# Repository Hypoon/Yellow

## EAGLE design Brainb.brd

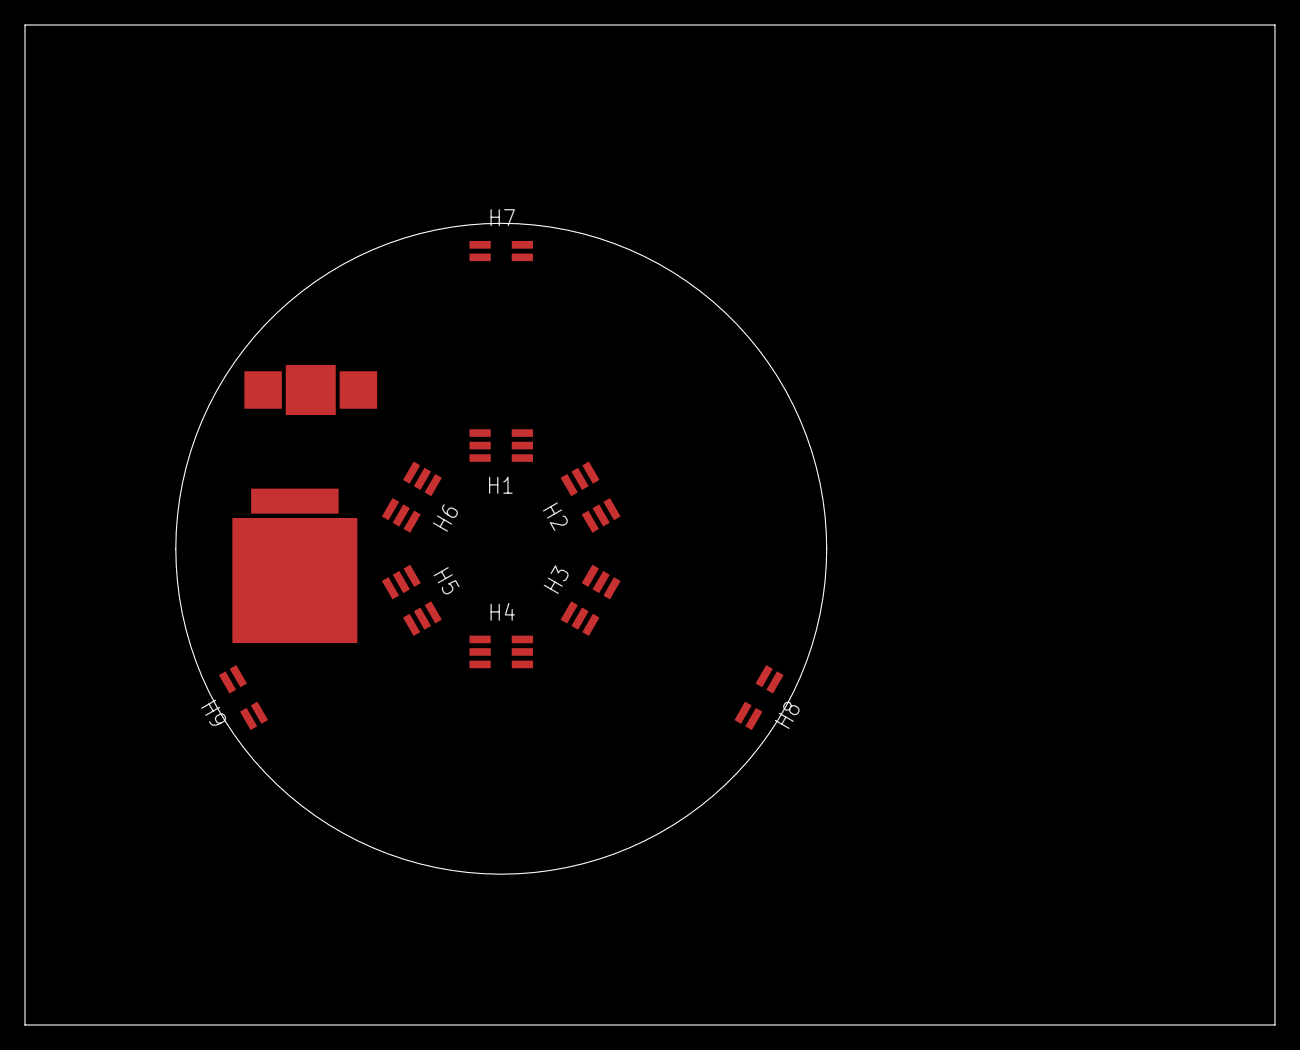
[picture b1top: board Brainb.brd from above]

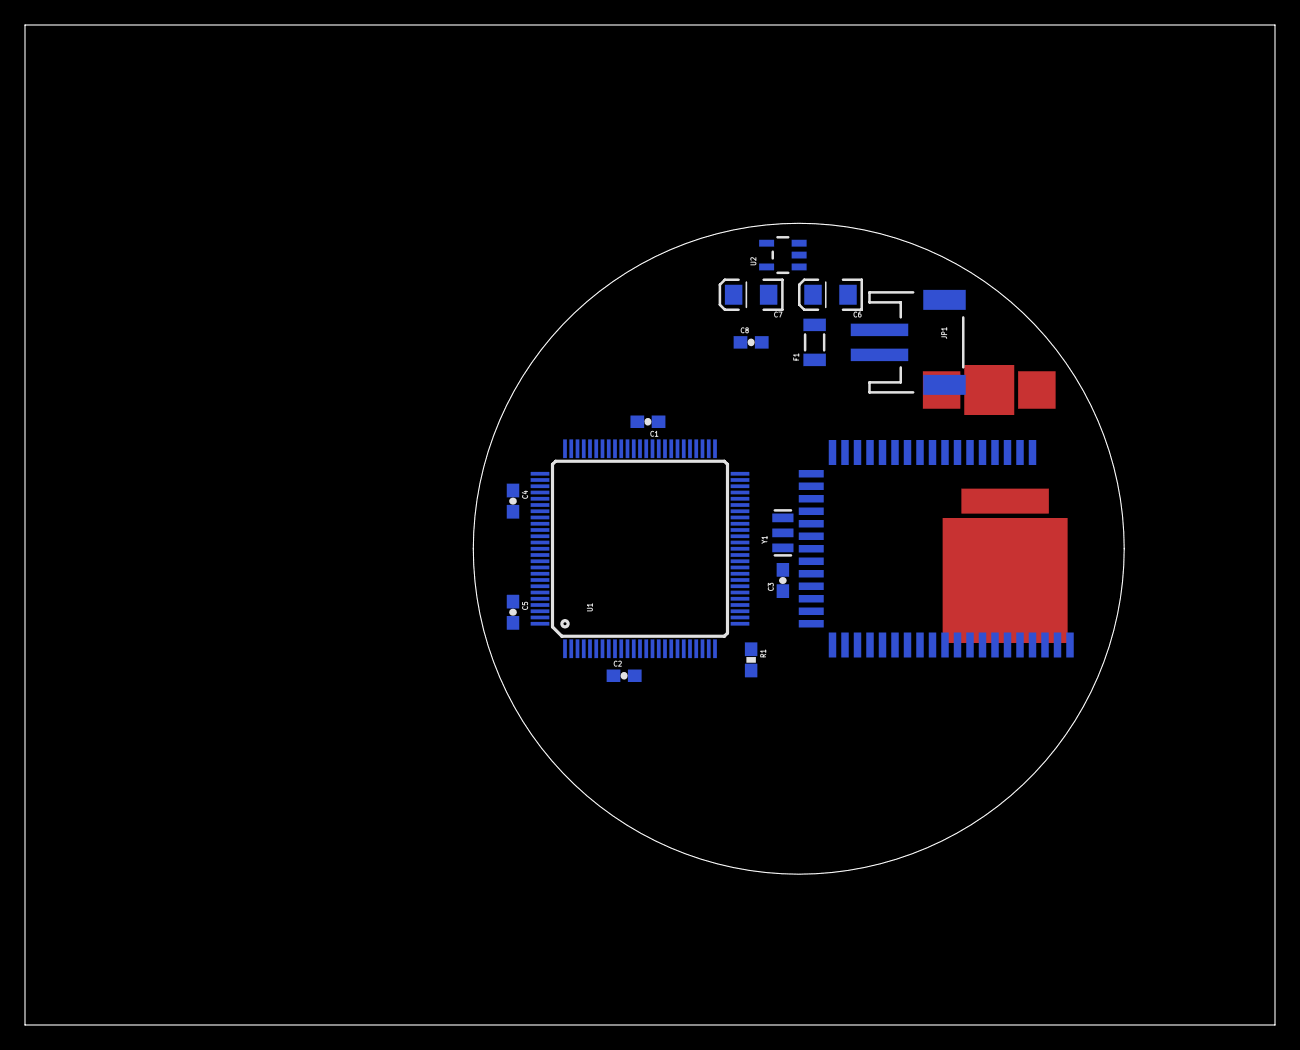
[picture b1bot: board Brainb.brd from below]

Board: 2 copper layers, 100.0 x 80.0 mm, 24 parts (15 on the bottom side), 8 nets, no tracks yet.

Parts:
C1, C2, C3, C4, C5, C8: 0.1uF; 0603-CAP
C6, C7: 10uF; EIA3216
F1: PTCSMD; PTC-1206
H1, H2, H3, H4, H5, H6: 3X2F_1MM_SMD
H7, H8, H9: 2X2F_1MM_SMD
IC1: WT32WT32; WT32
JP1: JST-2-SMD
R1: 10k; 0603-RES
U1: ATMEGA2560AU; TQFP100
U2: MIC5219-3.3; SOT23-5
Y1: 8MHz; RESONATOR-SMD

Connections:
+3V3: C1.1, C2.1, C3.1, C4.1, C7.A, C8.1, R1.2, U1.10, U1.31, U1.61, U1.80, U1.100, U2.5
GND: C1.2, C2.2, C3.2, C4.2, C5.2, C6.C, C7.C, C8.2, JP1.1, U1.11, U1.32, U1.62, U1.81, U1.99, U2.2, Y1.2
unnamed: C5.1, U1.98
unnamed: U1.34, Y1.3
unnamed: U1.33, Y1.1
unnamed: F1.1, JP1.2
unnamed: R1.1, U1.30
unnamed: C6.A, F1.2, U2.1, U2.3

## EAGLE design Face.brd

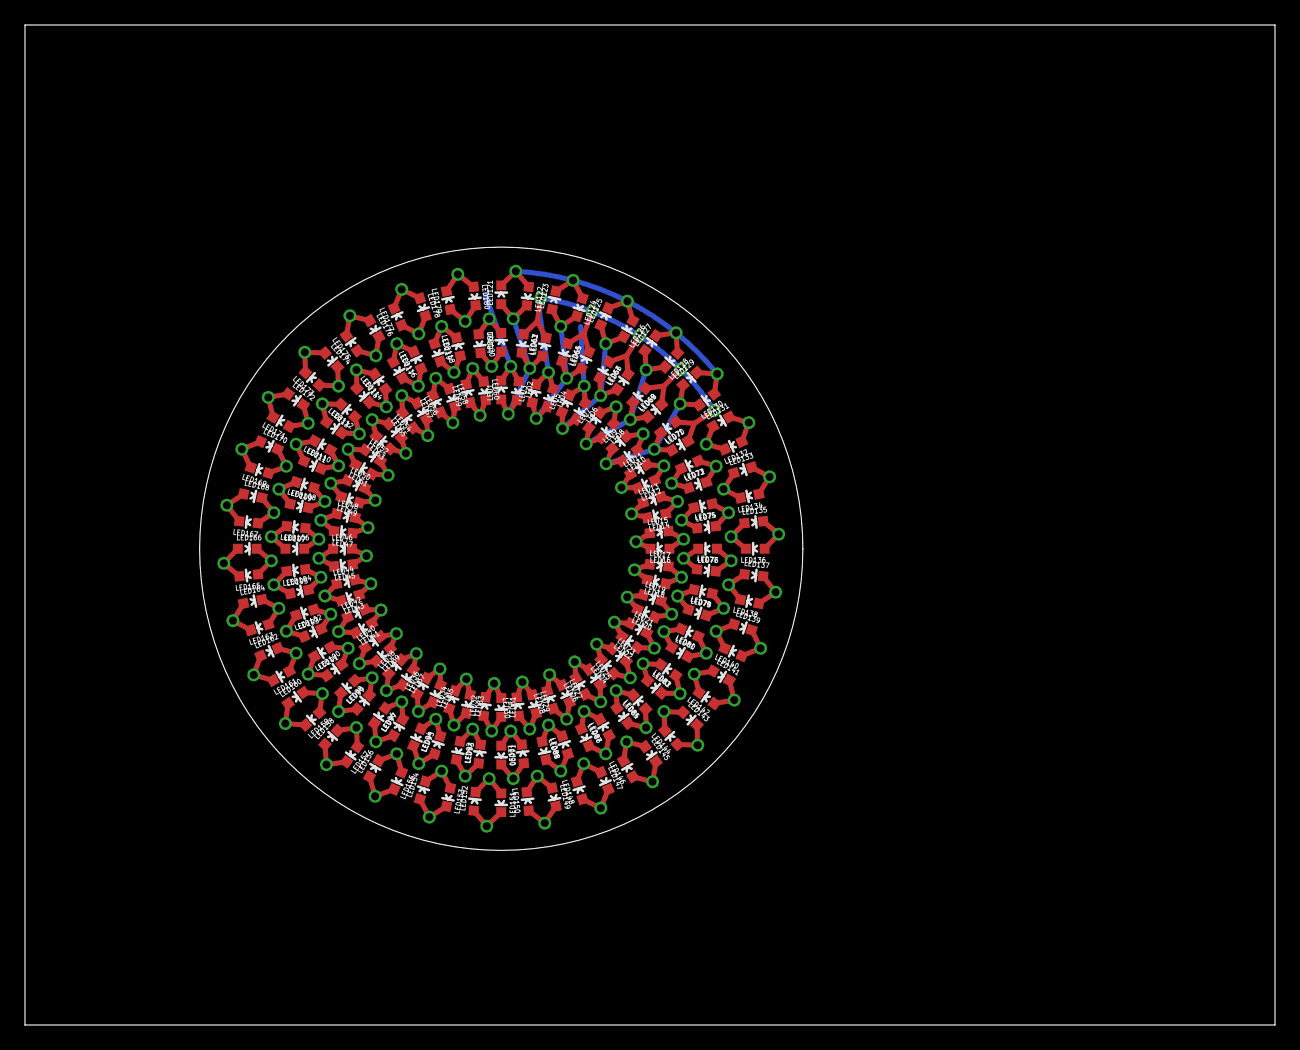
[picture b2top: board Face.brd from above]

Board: 2 copper layers, 100.0 x 80.0 mm, 180 parts (0 on the bottom side), 158 nets.

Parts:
LED1, LED2, LED3, LED4, LED5, LED6, LED7, LED8, LED9, LED10, LED11, LED12, LED13, LED14, LED15, LED16, LED17, LED18, LED19, LED20, LED21, LED22, LED23, LED24, LED25, LED26, LED27, LED28, LED29, LED30, LED31, LED32, LED33, LED34, LED35, LED36, LED37, LED38, LED39, LED40, LED41, LED42, LED43, LED44, LED45, LED46, LED47, LED48, LED49, LED50, LED51, LED52, LED53, LED54, LED55, LED56, LED57, LED58, LED59, LED60, LED61, LED62, LED63, LED64, LED65, LED66, LED67, LED68, LED69, LED70, LED71, LED72, LED73, LED74, LED75, LED76, LED77, LED78, LED79, LED80, LED81, LED82, LED83, LED84, LED85, LED86, LED87, LED88, LED89, LED90, LED91, LED92, LED93, LED94, LED95, LED96, LED97, LED98, LED99, LED100, LED101, LED102, LED103, LED104, LED105, LED106, LED107, LED108, LED109, LED110, LED111, LED112, LED113, LED114, LED115, LED116, LED117, LED118, LED119, LED120, LED121, LED122, LED123, LED124, LED125, LED126, LED127, LED128, LED129, LED130, LED131, LED132, LED133, LED134, LED135, LED136, LED137, LED138, LED139, LED140, LED141, LED142, LED143, LED144, LED145, LED146, LED147, LED148, LED149, LED150, LED151, LED152, LED153, LED154, LED155, LED156, LED157, LED158, LED159, LED160, LED161, LED162, LED163, LED164, LED165, LED166, LED167, LED168, LED169, LED170, LED171, LED172, LED173, LED174, LED175, LED176, LED177, LED178, LED179, LED180: RED; LED-0603

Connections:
unnamed: LED1.A, LED2.C, LED62.C, LED63.A, LED121.A, LED122.C
unnamed: LED3.A, LED4.C, LED64.C, LED65.A, LED123.A, LED124.C
unnamed: LED5.A, LED6.C, LED66.C, LED67.A, LED125.A, LED126.C
unnamed: LED7.A, LED8.C, LED68.C, LED69.A, LED127.A, LED128.C
unnamed: LED9.A, LED10.C, LED70.C, LED71.A, LED129.A, LED130.C
unnamed: LED11.A, LED12.C
unnamed: LED13.A, LED14.C
unnamed: LED15.A, LED16.C
unnamed: LED17.A, LED18.C
unnamed: LED19.A, LED20.C
unnamed: LED21.A, LED22.C
unnamed: LED23.A, LED24.C
unnamed: LED25.A, LED26.C
unnamed: LED27.A, LED28.C
unnamed: LED29.A, LED30.C
unnamed: LED31.A, LED32.C
unnamed: LED33.A, LED34.C
unnamed: LED35.A, LED36.C
unnamed: LED37.A, LED38.C
unnamed: LED39.A, LED40.C
unnamed: LED41.A, LED42.C
unnamed: LED43.A, LED44.C
unnamed: LED45.A, LED46.C
unnamed: LED47.A, LED48.C
unnamed: LED49.A, LED50.C
unnamed: LED51.A, LED52.C
unnamed: LED53.A, LED54.C
unnamed: LED55.A, LED56.C
unnamed: LED57.A, LED58.C
unnamed: LED59.A, LED60.C
unnamed: LED72.C, LED73.A
unnamed: LED74.C, LED75.A
unnamed: LED76.C, LED77.A
unnamed: LED78.C, LED79.A
unnamed: LED80.C, LED81.A
unnamed: LED82.C, LED83.A
unnamed: LED84.C, LED85.A
unnamed: LED86.C, LED87.A
unnamed: LED88.C, LED89.A
unnamed: LED90.C, LED91.A
unnamed: LED92.C, LED93.A
unnamed: LED94.C, LED95.A
unnamed: LED96.C, LED97.A
unnamed: LED98.C, LED99.A
unnamed: LED100.C, LED101.A
unnamed: LED102.C, LED103.A
unnamed: LED104.C, LED105.A
unnamed: LED106.C, LED107.A
unnamed: LED108.C, LED109.A
unnamed: LED110.C, LED111.A
unnamed: LED112.C, LED113.A
unnamed: LED114.C, LED115.A
unnamed: LED116.C, LED117.A
unnamed: LED118.C, LED119.A
unnamed: LED61.A, LED120.C
unnamed: LED131.A, LED132.C
unnamed: LED133.A, LED134.C
unnamed: LED135.A, LED136.C
unnamed: LED137.A, LED138.C
unnamed: LED139.A, LED140.C
unnamed: LED141.A, LED142.C
unnamed: LED143.A, LED144.C
unnamed: LED145.A, LED146.C
unnamed: LED147.A, LED148.C
unnamed: LED149.A, LED150.C
unnamed: LED151.A, LED152.C
unnamed: LED153.A, LED154.C
unnamed: LED155.A, LED156.C
unnamed: LED157.A, LED158.C
unnamed: LED159.A, LED160.C
unnamed: LED161.A, LED162.C
unnamed: LED163.A, LED164.C
unnamed: LED165.A, LED166.C
unnamed: LED167.A, LED168.C
unnamed: LED169.A, LED170.C
unnamed: LED171.A, LED172.C
unnamed: LED173.A, LED174.C
unnamed: LED175.A, LED176.C
unnamed: LED177.A, LED178.C
unnamed: LED179.A, LED180.C
unnamed: LED1.C, LED2.A, LED3.C, LED4.A, LED5.C, LED6.A, LED7.C, LED8.A, LED9.C, LED10.A
unnamed: LED11.C, LED12.A
unnamed: LED13.C, LED14.A
unnamed: LED15.C, LED16.A
unnamed: LED17.C, LED18.A
unnamed: LED19.C, LED20.A
unnamed: LED21.C, LED22.A
unnamed: LED23.C, LED24.A
unnamed: LED25.C, LED26.A
unnamed: LED27.C, LED28.A
unnamed: LED29.C, LED30.A
unnamed: LED31.C, LED32.A
unnamed: LED33.C, LED34.A
unnamed: LED35.C, LED36.A
unnamed: LED37.C, LED38.A
unnamed: LED39.C, LED40.A
unnamed: LED41.C, LED42.A
unnamed: LED43.C, LED44.A
unnamed: LED45.C, LED46.A
unnamed: LED47.C, LED48.A
unnamed: LED49.C, LED50.A
unnamed: LED51.C, LED52.A
unnamed: LED53.C, LED54.A
unnamed: LED55.C, LED56.A
unnamed: LED57.C, LED58.A
unnamed: LED59.C, LED60.A
unnamed: LED62.A, LED63.C, LED64.A, LED65.C, LED66.A, LED67.C, LED68.A, LED69.C, LED70.A, LED71.C
unnamed: LED72.A, LED73.C
unnamed: LED74.A, LED75.C
unnamed: LED76.A, LED77.C
unnamed: LED78.A, LED79.C
unnamed: LED80.A, LED81.C
unnamed: LED82.A, LED83.C
unnamed: LED84.A, LED85.C
unnamed: LED86.A, LED87.C
unnamed: LED88.A, LED89.C
unnamed: LED90.A, LED91.C
unnamed: LED92.A, LED93.C
unnamed: LED94.A, LED95.C
unnamed: LED96.A, LED97.C
unnamed: LED98.A, LED99.C
unnamed: LED100.A, LED101.C
unnamed: LED102.A, LED103.C
unnamed: LED104.A, LED105.C
unnamed: LED106.A, LED107.C
unnamed: LED108.A, LED109.C
unnamed: LED110.A, LED111.C
unnamed: LED112.A, LED113.C
unnamed: LED114.A, LED115.C
unnamed: LED116.A, LED117.C
unnamed: LED118.A, LED119.C
unnamed: LED61.C, LED120.A
unnamed: LED121.C, LED122.A, LED123.C, LED124.A, LED125.C, LED126.A, LED127.C, LED128.A, LED129.C, LED130.A
unnamed: LED131.C, LED132.A
unnamed: LED133.C, LED134.A
unnamed: LED135.C, LED136.A
unnamed: LED137.C, LED138.A
unnamed: LED139.C, LED140.A
unnamed: LED141.C, LED142.A
unnamed: LED143.C, LED144.A
unnamed: LED145.C, LED146.A
unnamed: LED147.C, LED148.A
unnamed: LED149.C, LED150.A
unnamed: LED151.C, LED152.A
unnamed: LED153.C, LED154.A
unnamed: LED155.C, LED156.A
unnamed: LED157.C, LED158.A
unnamed: LED159.C, LED160.A
unnamed: LED161.C, LED162.A
unnamed: LED163.C, LED164.A
unnamed: LED165.C, LED166.A
unnamed: LED167.C, LED168.A
unnamed: LED169.C, LED170.A
unnamed: LED171.C, LED172.A
unnamed: LED173.C, LED174.A
unnamed: LED175.C, LED176.A
unnamed: LED177.C, LED178.A
unnamed: LED179.C, LED180.A

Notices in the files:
parts and their libraries:
SparkFun-DigitalIC: Licensing: CC v3.0 Share-Alike You are welcome to use this library for commercial purposes.
